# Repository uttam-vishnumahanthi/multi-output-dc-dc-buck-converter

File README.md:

# Multi-Output DC-DC Buck Converter

A compact, high-efficiency multi-output DC-DC buck converter designed to convert a variable **16–28 V DC input** into regulated **3.3 V**, **5 V**, and **12 V** outputs. This project focuses on reliable power conversion, PCB optimization, modular hardware design, and future integration of protection circuitry for embedded and autonomous systems.

---

## Project Overview

This project aims to develop a compact power supply module capable of providing multiple regulated voltage rails from a single DC source. The converter is intended for embedded electronics, robotics, autonomous systems, and other applications requiring stable and efficient power distribution.

The current implementation includes a fully designed and tested **5 V buck converter** using the **LM2596-ADJ** switching regulator. Future work includes the implementation of 3.3 V and 12 V outputs, advanced protection features, and PCB optimization.

---

## Features

- Input Voltage: **16 V – 28 V DC**
- Regulated Outputs:
  - 3.3 V
  - 5 V
  - 12 V
- High-efficiency buck converter architecture
- LM2596-ADJ based design
- Compact PCB layout
- Low ripple output
- Hardware implementation and testing
- KiCad PCB design
- Proteus simulation
- Modular architecture for future expansion

---

## Hardware Specifications

| Parameter | Value |
|-----------|--------|
| Input Voltage | 16–28 V DC |
| Output Voltages | 3.3 V, 5 V, 12 V |
| Converter Type | Buck (Step-Down) |
| Main Controller | LM2596-ADJ |
| PCB Design Tool | KiCad |
| Simulation Tool | Proteus Professional |

---

## Design Workflow

1. Requirement Analysis
2. Buck Converter Design
3. Component Selection
4. Simulation in Proteus
5. PCB Design in KiCad
6. Hardware Assembly
7. Performance Testing
8. Future Design Improvements

---

## Current Progress

✔ Requirement analysis completed

✔ LM2596 buck converter designed

✔ Simulation completed

✔ PCB designed in KiCad

✔ Hardware assembled

✔ Initial hardware testing completed

✔ 3.3 V output implementation

✔ 12 V output implementation

⬜ Protection circuitry

⬜ Thermal optimization

⬜ EMI/EMC improvements

---

## Future Improvements

- Over Voltage Protection (OVP)
- Over Current Protection (OCP)
- Reverse Polarity Protection
- Thermal Shutdown
- EMI/EMC Optimization
- Improved PCB Layout
- Multi-output regulation
- Military-grade reliability practices
- Efficiency optimization
- Wide-temperature operation

---

## Applications

- Embedded Systems
- Robotics
- Autonomous Vehicles
- Industrial Electronics
- Sensor Power Distribution
- Automotive Electronics
- Research and Development Platforms

---

## Tools Used

- KiCad
- Proteus Professional
- LM2596-ADJ
- LM5145
- Digital Multimeter
- Oscilloscope
- Soldering Workstation

---

## Author

**Uttam V**

Electronics and Computer Engineering

---

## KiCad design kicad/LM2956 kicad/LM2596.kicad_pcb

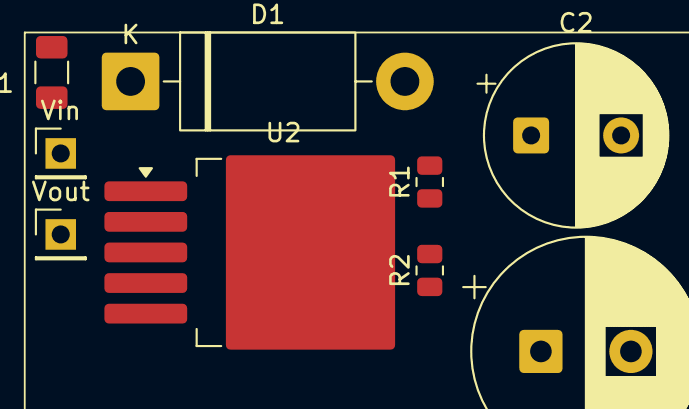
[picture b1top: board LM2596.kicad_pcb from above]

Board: 2 copper layers, 9 parts (0 on the bottom side), 6 nets, no tracks yet.

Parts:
C1: 680uf; CP_Radial_D12.5mm_P5.00mm
C2: 220uf; CP_Radial_D10.0mm_P5.00mm
D1: D_Schottky; D_DO-201AD_P15.24mm_Horizontal
F1: Fuse; Fuse_1206_3216Metric
R1: 1k; R_0805_2012Metric
R2: 3.09k; R_0805_2012Metric
U2: LM2596S-ADJ; TO-263-5_TabPin3
Vin: Conn_01x02; PinHeader_1x01_P2.54mm_Vertical
Vout: Conn_01x02; PinHeader_1x01_P2.54mm_Vertical

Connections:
unnamed: C1.2, C2.2, D1.2 (A), R1.2, U2.3 (GND), U2.5 (~ON/OFF)
unnamed: D1.1 (K), U2.2 (OUT)
unnamed: F1.1, Vin.1
unnamed: C2.1, R2.2, Vout.1
unnamed: R1.1, R2.1, U2.4 (FB)
unnamed: C1.1, F1.2, U2.1 (VIN)

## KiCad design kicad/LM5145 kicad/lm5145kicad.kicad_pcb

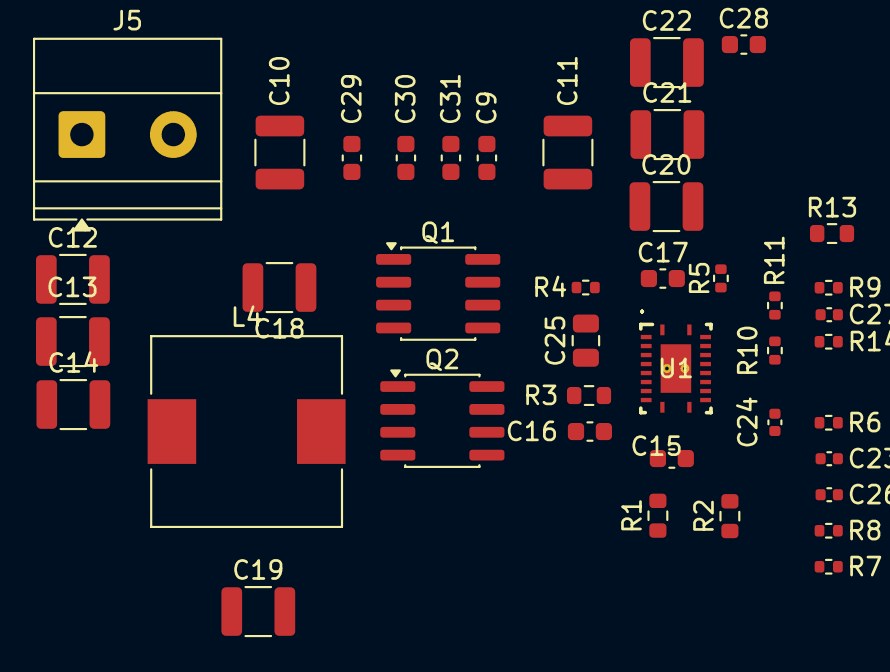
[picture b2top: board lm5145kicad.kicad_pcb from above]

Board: 2 copper layers, 41 parts (0 on the bottom side), 21 nets, no tracks yet.

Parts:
C9, C29, C30, C31: GRM188R72A103KA01D; C_0603_1608Metric
C10, C11, C12, C13, C14: C3225X7S2A475K200AE; C_1210_3225Metric
C15, C16, C28: CGA3E3X7S2A104K080AB; C_0603_1608Metric
C17: 885012006073; C_0603_1608Metric
C18, C19, C20, C21, C22: TMK325B7226KMHT; C_1210_3225Metric
C23: GRM155R71C472KA01D; C_0402_1005Metric
C24: CGA2B2C0G1H101J050BA; C_0402_1005Metric
C25: GRM21BR71E225KA73L; C_0805_2012Metric
C26: C1005X7R1C473K050BC; C_0402_1005Metric
C27: CGA2B2X7R1H102K050BA; C_0402_1005Metric
J5: Conn_01x02_Pin; TerminalBlock_Phoenix_MKDS-1,5-2-5.08_1x02_P5.08mm_Horizont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
L4: VCHA105D-6R8MS6; L_10.4x10.4_H4.8
Q1: NVMFS6B25NLT1G; SOIC-8_3.9x4.9mm_P1.27mm
Q2: NVMFS6B14NLT1G; SOIC-8_3.9x4.9mm_P1.27mm
R1, R3: ERJ-3RQF2R2V; R_0603_1608Metric
R2: CRCW0603100KFKEA; R_0603_1608Metric
R4: CRCW0402619RFKED; R_0402_1005Metric
R5: CRCW040220K0FKED; R_0402_1005Metric
R6: CRCW04028K06FKED; R_0402_1005Metric
R7: CRCW040210K5FKED; R_0402_1005Metric
R8: CRCW040224K9FKED; R_0402_1005Metric
R9: CRCW040251R1FKED; R_0402_1005Metric
R10: CRCW04021K50FKED; R_0402_1005Metric
R11: CRCW040221K0FKED; R_0402_1005Metric
R13: CRCW060320K0FKEA; R_0603_1608Metric
R14: CRCW040236K5FKED; R_0402_1005Metric
U1: LM5146QRGYRQ1; RGY0020B

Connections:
/COMP: C23.1, C24.1, U1.4 (COMP)
/FB: C24.2, C27.2, R6.1, R11.2, U1.5 (FB)
/HO: Q1.4 (G), U1.18 (HO)
/ILIM: C17.1, R4.1, U1.11 (ILIM)
/LO: Q2.4 (G), U1.13 (LO)
/RT: R8.1, U1.2 (RT)
/SW: C16.2, L4.1, Q1.1 (S), Q1.2 (S), Q1.3 (S), Q2.5 (D), R4.2, U1.19 (SW)
/VOUT: C18.1, C19.1, C20.1, C21.1, C22.1, C28.1, L4.2, R9.1, R11.1
AGND: C26.1, R7.1, R8.2, R10.1, U1.6 (AGND)
EN: R2.2, R7.2, U1.1 (EN/UVLO)
GND: C9.2, C10.2, C11.2, C12.2, C13.2, C14.2, C15.2, C17.2, C18.2, C19.2, C20.2, C21.2, C22.2, C25.2, C28.2, C29.2, C30.2, C31.2, J5.2, Q2.1 (S), Q2.2 (S), Q2.3 (S), U1.12 (PGND), U1.15 (EP), U1.21 (EP)
unnamed: C16.1, R3.2
unnamed: C23.2, R6.2
unnamed: C27.1, R9.2
unnamed: R3.1, U1.17 (BST)
unnamed: C15.1, R1.2, U1.20 (VIN)
PGOOD: R5.2, U1.10 (PGOOD)
SS: C26.2, U1.3 (SS/TRK)
SYNCIN: R13.2, U1.8 (SYNCIN)
VCC: C25.1, R5.1, R13.1, U1.14 (VCC)
VIN: C9.1, C10.1, C11.1, C12.1, C13.1, C14.1, C29.1, C30.1, C31.1, J5.1, Q1.5 (D), R1.1, R2.1
